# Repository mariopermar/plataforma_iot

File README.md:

# plataforma_iot
Plataforma de iot con hardware propio.

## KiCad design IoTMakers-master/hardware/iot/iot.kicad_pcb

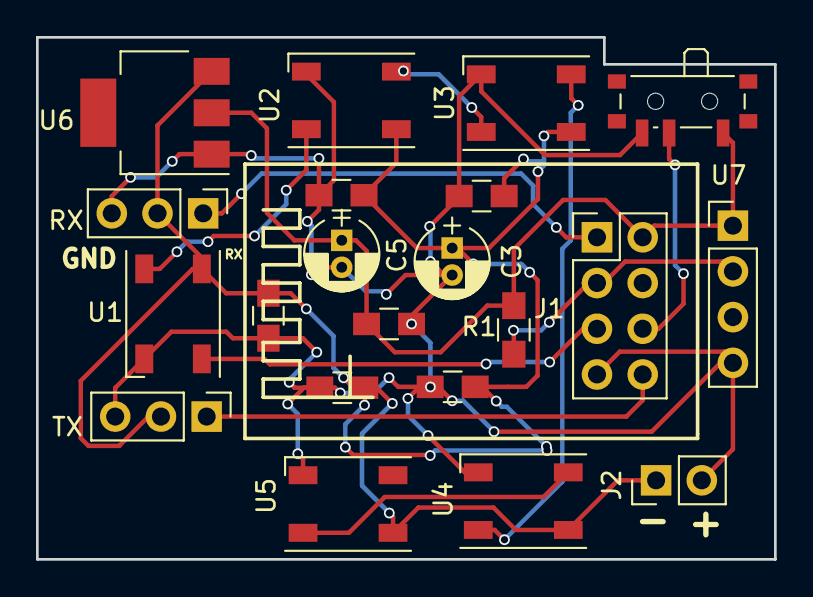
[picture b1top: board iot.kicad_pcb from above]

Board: 2 copper layers, 41.0 x 29.0 mm, 14 parts (0 on the bottom side), 11 nets.

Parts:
C3: 10uF; CP_Radial_D4.0mm_P1.50mm
C5: 22uF; CP_Radial_D4.0mm_P1.50mm
J1: Conn_02x04_Top_Bottom; Pin_Header_Straight_2x04_Pitch2.54mm
J2: Conn_01x02; Pin_Header_Straight_1x02_Pitch2.54mm
R1: 4k7; R_0805_HandSoldering
RX: Conn_01x03; Pin_Header_Straight_1x03_Pitch2.54mm
TX: Conn_01x03; Pin_Header_Straight_1x03_Pitch2.54mm
U1, U2, U3, U4, U5: WS2812b; LED_WS2812B-PLCC4
U6: LM1117-3.3; SOT-223
U7: DHT11; Pin_Header_Straight_1x04_Pitch2.54mm

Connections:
+3V3: C5.1, J1.5, R1.1, U6.2, U7.1
+5V: C3.1, J2.1, RX.2, TX.2, U1.1, U2.1, U3.1, U4.1, U5.1, U6.3
/GPIO_0: J1.2, R1.2, U7.2
/GPIO_2: J1.3, U1.4
/RX: J1.1, RX.1
/TX: J1.8, TX.1
GND: C3.2, C5.2, J1.4, J2.2, RX.3, TX.3, U1.3, U2.3, U3.3, U4.3, U5.3, U6.1, U7.4
unnamed: U1.2, U2.4
unnamed: U2.2, U3.4
unnamed: U3.2, U4.4
unnamed: U4.2, U5.4

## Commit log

2018-03-03 Hemos empezado a crear el esquema.
    Nos hemos quedado conectando los leds despues de crear los componentes que no existian.
